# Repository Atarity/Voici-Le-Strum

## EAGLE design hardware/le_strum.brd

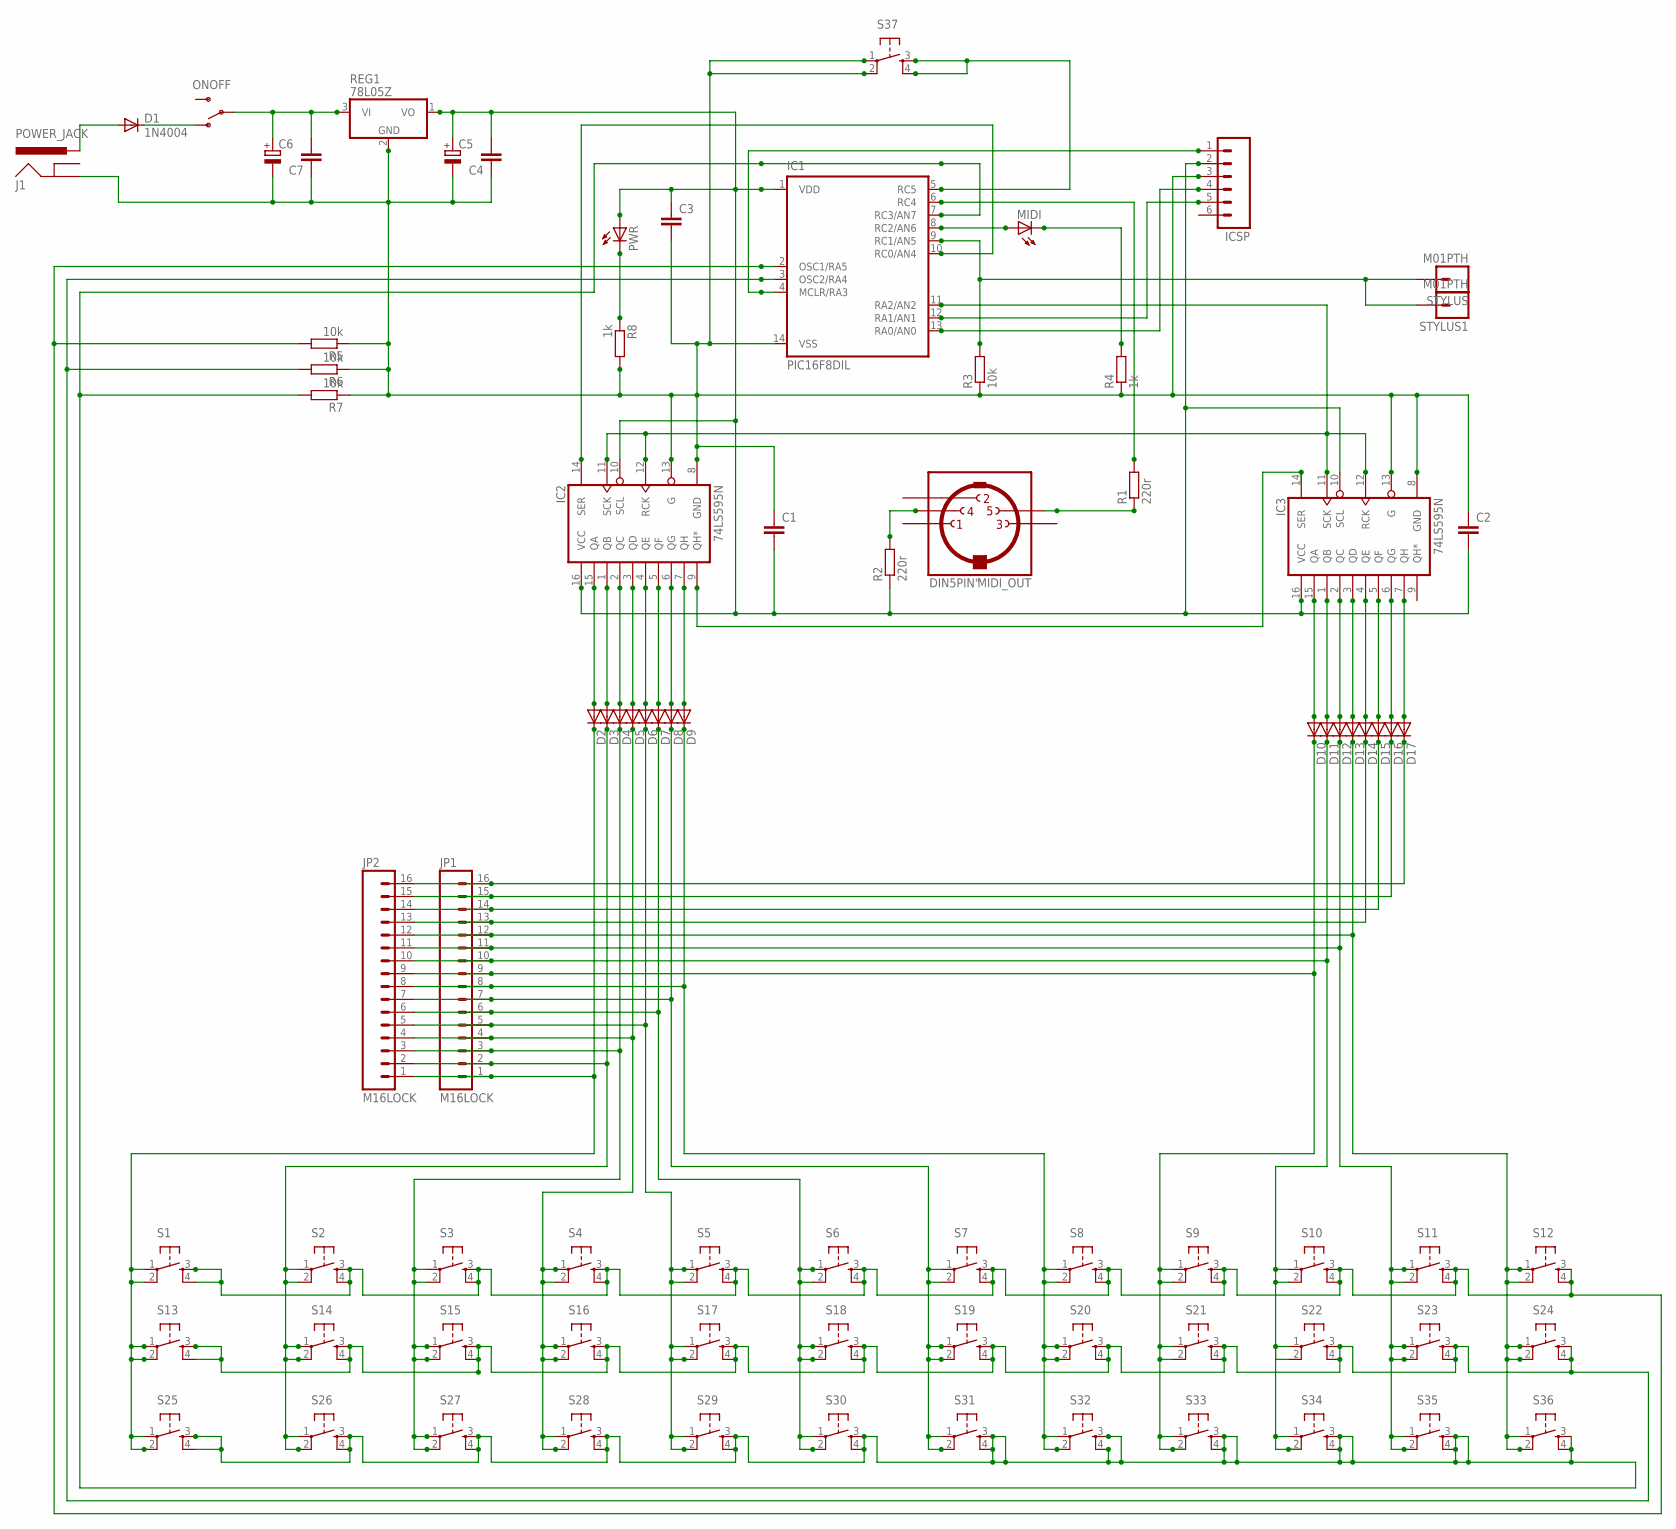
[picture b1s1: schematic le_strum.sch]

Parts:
C1, C2, C3, C4, C7: C-EU025-024X044; C025-024X044
C5, C6: CPOL-EUE2-5; E2-5
D1: 1N4004; DO41-10
D2, D3, D4, D5, D6, D7, D8, D9, D10, D11, D12, D13, D14, D15, D16, D17: DIODE-D-5; D-5
IC1: PIC16F8DIL; DIL14
IC2, IC3: 74LS595N; DIL16
ICSP: M06SIP; 1X06
J1: POWER_JACK; POWER_JACK_PTH
JP1, JP2: M16LOCK; 1X16_LOCK
MIDI: LED3MM
MIDI_OUT: DIN5PIN"; TRUCONN90
ONOFF: SWITCH-SPSTPTH; SWITCH-SPDT
PWR: LED3MM
R1, R2: 220r; 0207/7
R3, R5, R6, R7: 10k; 0207/7
R4, R8: 1k; 0207/7
REG1: 78L05Z; TO92
S1, S2, S3, S4, S5, S6, S7, S8, S9, S10, S11, S12, S13, S14, S15, S16, S17, S18, S19, S20, S21, S22, S23, S24, S25, S26, S27, S28, S29, S30, S31, S32, S33, S34, S35, S36, S37: TAC_SWITCHPTH; TACTILE-PTH
STYLUS, STYLUS1: M01PTH; 1X01

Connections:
CARRY: IC2.9 (QH*), IC3.14 (SER)
CLK: IC1.11 (RA2/AN2), IC2.11 (SCK), IC2.12 (RCK), IC3.11 (SCK), IC3.12 (RCK)
GND: C1.1, C2.1, C3.2, C4.1, C5.-, C6.-, C7.1, IC1.14 (VSS), IC2.8 (GND), IC2.13 (G), IC3.8 (GND), IC3.13 (G), ICSP.3, J1.GND, R3.1, R4.1, R5.1, R6.1, R7.1, R8.2, REG1.2 (GND), S37.1, S37.2
LINE1: D2.C, JP1.1, JP2.1, S1.1, S1.2, S13.1, S13.2, S25.1, S25.2
LINE2: D3.C, JP1.2, JP2.2, S2.1, S2.2, S14.1, S14.2, S26.1, S26.2
LINE3: D4.C, JP1.3, JP2.3, S3.1, S3.2, S15.1, S15.2, S27.1, S27.2
LINE4: D5.C, JP1.4, JP2.4, S4.1, S4.2, S16.1, S16.2, S28.1, S28.2
LINE5: D6.C, JP1.5, JP2.5, S5.1, S5.2, S17.1, S17.2, S29.1, S29.2
LINE6: D7.C, JP1.6, JP2.6, S6.1, S6.2, S18.1, S18.2, S30.1, S30.2
LINE7: D8.C, JP1.7, JP2.7, S7.1, S7.2, S19.1, S19.2, S31.1, S31.2
LINE8: D9.C, JP1.8, JP2.8, S8.1, S8.2, S20.1, S20.2, S32.1, S32.2
LINE9: D10.C, JP1.9, JP2.9, S9.1, S9.2, S21.1, S21.2, S33.1, S33.2
LINE10: D11.C, JP1.10, JP2.10, S10.1, S10.2, S22.1, S22.2, S34.1, S34.2
LINE11: D12.C, JP1.11, JP2.11, S11.1, S11.2, S23.1, S23.2, S35.1, S35.2
LINE12: D13.C, JP1.12, JP2.12, S12.1, S12.2, S24.1, S24.2, S36.1, S36.2
LINE13: D14.C, JP1.13, JP2.13
LINE14: D15.C, JP1.14, JP2.14
LINE15: D16.C, JP1.15, JP2.15
LINE16: D17.C, JP1.16, JP2.16
unnamed: IC1.2 (OSC1/RA5), R5.2, S1.3, S1.4, S2.3, S2.4, S3.3, S3.4, S4.3, S4.4, S5.3, S5.4, S6.3, S6.4, S7.3, S7.4, S8.3, S8.4, S9.3, S9.4, S10.3, S10.4, S11.3, S11.4, S12.3, S12.4
unnamed: D1.A, J1.PWR
unnamed: D1.C, ONOFF.1 (O)
unnamed: IC1.13 (RA0/AN0), ICSP.4
unnamed: D2.A, IC2.15 (QA)
unnamed: D3.A, IC2.1 (QB)
unnamed: D4.A, IC2.2 (QC)
unnamed: D5.A, IC2.3 (QD)
unnamed: D6.A, IC2.4 (QE)
unnamed: D7.A, IC2.5 (QF)
unnamed: D8.A, IC2.6 (QG)
unnamed: IC1.9 (RC1/AN5), R3.2, STYLUS.1, STYLUS1.1
unnamed: D9.A, IC2.7 (QH)
unnamed: D10.A, IC3.15 (QA)
unnamed: D11.A, IC3.1 (QB)
unnamed: D12.A, IC3.2 (QC)
unnamed: D13.A, IC3.3 (QD)
unnamed: D14.A, IC3.4 (QE)
unnamed: D15.A, IC3.5 (QF)
unnamed: D16.A, IC3.6 (QG)
unnamed: D17.A, IC3.7 (QH)
unnamed: IC1.5 (RC5), S37.3, S37.4
unnamed: IC1.7 (RC3/AN7), R7.2, S25.3, S25.4, S26.3, S26.4, S27.3, S27.4, S28.3, S28.4, S29.3, S29.4, S30.3, S30.4, S31.3, S31.4, S32.3, S32.4, S33.3, S33.4, S34.3, S34.4, S35.3, S35.4, S36.3, S36.4
unnamed: IC1.10 (RC0/AN4), IC2.14 (SER)
unnamed: IC1.4 (MCLR/RA3), ICSP.1
unnamed: IC1.8 (RC2/AN6), MIDI.A
unnamed: IC1.12 (RA1/AN1), ICSP.5
unnamed: MIDI_OUT.5, R1.1
unnamed: IC1.6 (RC4), R1.2
unnamed: MIDI_OUT.4, R2.2
unnamed: IC1.3 (OSC2/RA4), R6.2, S13.3, S13.4, S14.3, S14.4, S15.3, S15.4, S16.3, S16.4, S17.3, S17.4, S18.3, S18.4, S19.3, S19.4, S20.3, S20.4, S21.3, S21.4, S22.3, S22.4, S23.3, S23.4, S24.3, S24.4
unnamed: MIDI.K (C), R4.2
unnamed: PWR.K (C), R8.1
unnamed: C6.+, C7.2, ONOFF.2, REG1.3 (VI)
VCC: C1.2, C2.2, C3.1, C4.2, C5.+, IC1.1 (VDD), IC2.10 (SCL), IC2.16 (VCC), IC3.10 (SCL), IC3.16 (VCC), ICSP.2, PWR.A, R2.1, REG1.1 (VO)

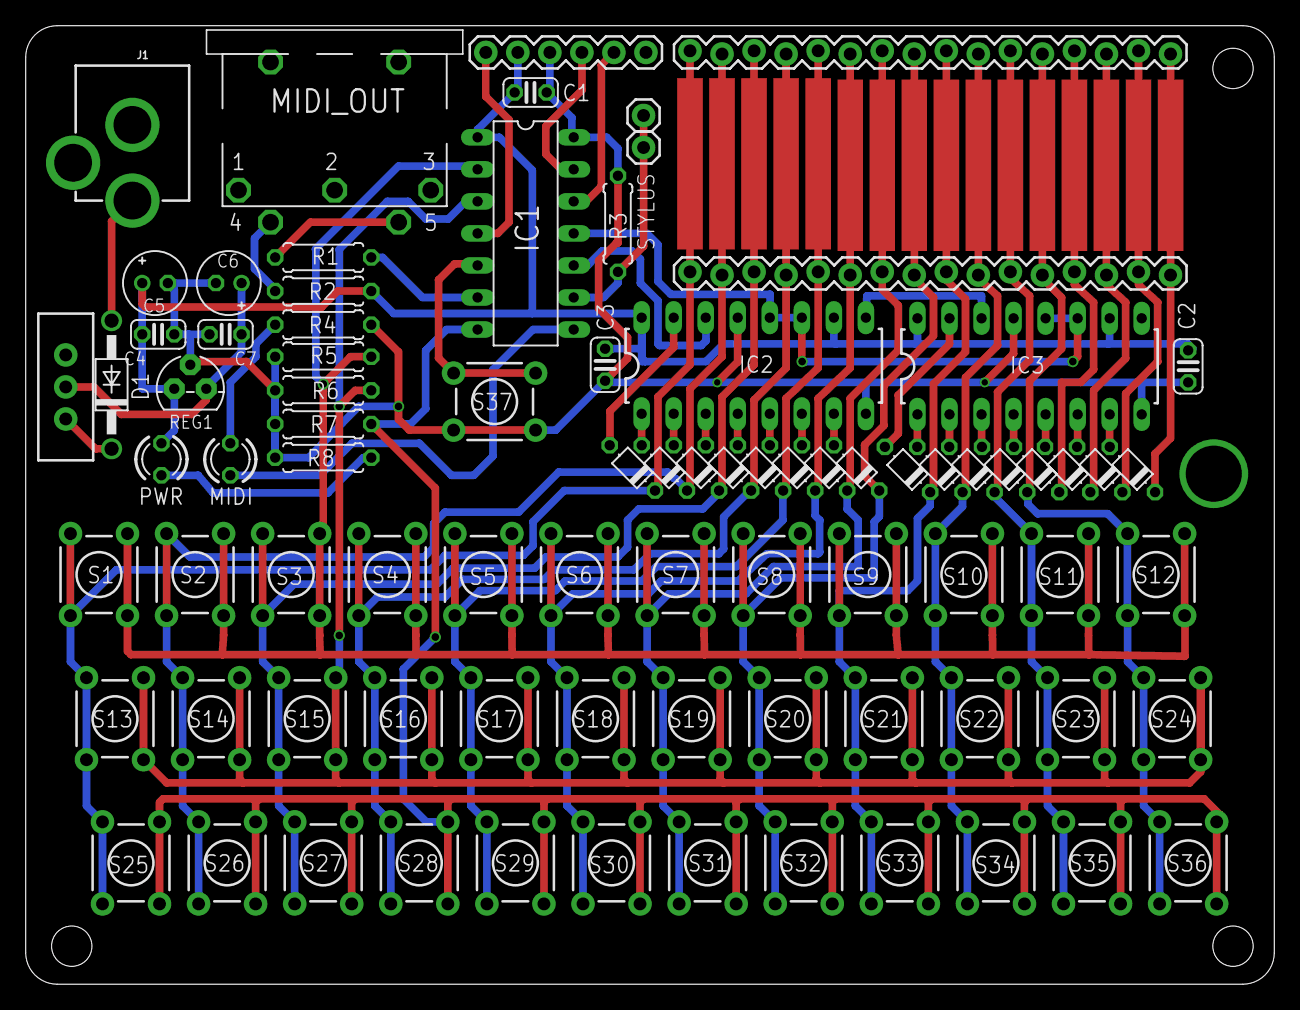
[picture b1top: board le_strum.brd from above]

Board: 2 copper layers, 99.0 x 76.0 mm, 83 parts (0 on the bottom side), 54 nets.

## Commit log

2021-09-28 power jack added
